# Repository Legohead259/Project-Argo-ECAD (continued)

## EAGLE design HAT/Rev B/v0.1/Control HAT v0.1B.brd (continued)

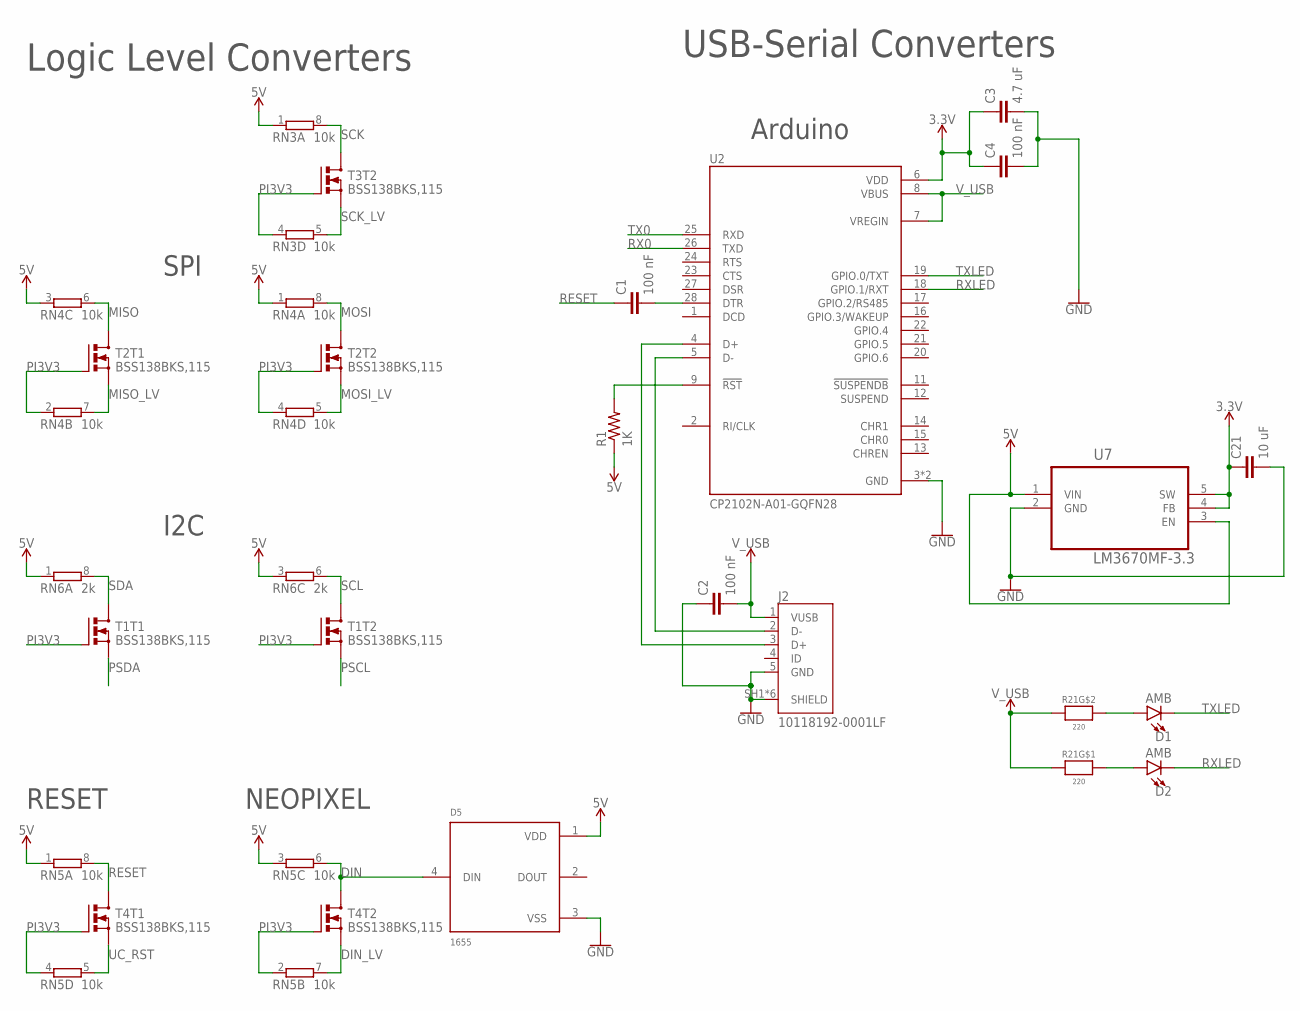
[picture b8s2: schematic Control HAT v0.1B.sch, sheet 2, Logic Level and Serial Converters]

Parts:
C1, C2, C4: 100 nF; C0603
C3: 4.7 uF; C0603
C21: 10 uF; C0603
D1, D2: AMB; LED-0603
D5: 1655; FCI_1655
J2: 10118192-0001LF; AMPHENOL_10118192-0001LF
R1: 1K; R0603
R21: 220; RESPACK_4X0603
RN3, RN4, RN5: 10k; EXB28V
RN6: 2k; EXB28V
T1, T2, T3, T4: BSS138BKS,115; SOT363
U2: CP2102N-A01-GQFN28; QFN50P500X500X80-29N
U7: LM3670MF-3.3; SOT95P284X122-5N

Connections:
3.3V: C3.1, C4.1, C21.1, U2.6 (VDD), U7.4 (FB), U7.5 (SW)
5V: D5.1 (VDD), R1.1, RN3.1, RN4.1, RN4.3 (1), RN5.1, RN5.3 (1), RN6.1, RN6.3 (1), U7.1 (VIN), U7.3 (EN); also elsewhere on the board
DIN: D5.4 (DIN), RN5.6 (2), T4.3 (D); also elsewhere on the board
DIN_LV: RN5.7 (2), T4.4 (S); also elsewhere on the board
GND: C2.1, C3.2, C4.2, C21.2, D5.3 (VSS), J2.5 (GND), J2.SH1 (SHIELD), J2.SH2 (SHIELD), J2.SH3 (SHIELD), J2.SH4 (SHIELD), J2.SH5 (SHIELD), J2.SH6 (SHIELD), U2.3 (GND), U2.29 (GND), U7.2 (GND); also elsewhere on the board
MISO: RN4.6 (2), T2.6 (D); also elsewhere on the board
MISO_LV: RN4.7 (2), T2.1 (S); also elsewhere on the board
MOSI: RN4.8 (2), T2.3 (D); also elsewhere on the board
MOSI_LV: RN4.5 (2), T2.4 (S); also elsewhere on the board
unnamed: J2.2 (D-), U2.5 (D-)
unnamed: J2.3 (D+), U2.4 (D+)
unnamed: R1.2, U2.9 (!RST)
unnamed: D1.A, R21.7 (2)
unnamed: D2.A, R21.8 (2)
unnamed: C1.2, U2.28 (DTR)
PI3V3: RN3.4 (1), RN4.2 (1), RN4.4 (1), RN5.2 (1), RN5.4 (1), T1.2 (G), T1.5 (G), T2.2 (G), T2.5 (G), T3.5 (G), T4.2 (G), T4.5 (G); also elsewhere on the board
PSCL: T1.4 (S); also elsewhere on the board
PSDA: T1.1 (S); also elsewhere on the board
RESET: C1.1, RN5.8 (2), T4.6 (D); also elsewhere on the board
RX0: U2.26 (TXD); also elsewhere on the board
RXLED: D2.C, U2.18 (GPIO.1/RXT)
SCK: RN3.8 (2), T3.3 (D); also elsewhere on the board
SCK_LV: RN3.5 (2), T3.4 (S); also elsewhere on the board
SCL: RN6.6 (2), T1.3 (D); also elsewhere on the board
SDA: RN6.8 (2), T1.6 (D); also elsewhere on the board
TX0: U2.25 (RXD); also elsewhere on the board
TXLED: D1.C, U2.19 (GPIO.0/TXT)
UC_RST: RN5.5 (2), T4.1 (S); also elsewhere on the board
V_USB: C2.2, J2.1 (VUSB), R21.1, R21.2 (1), U2.7 (VREGIN), U2.8 (VBUS)

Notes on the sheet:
Logic Level Converters
I2C
SPI
RESET
NEOPIXEL
USB-Serial Converters
Arduino

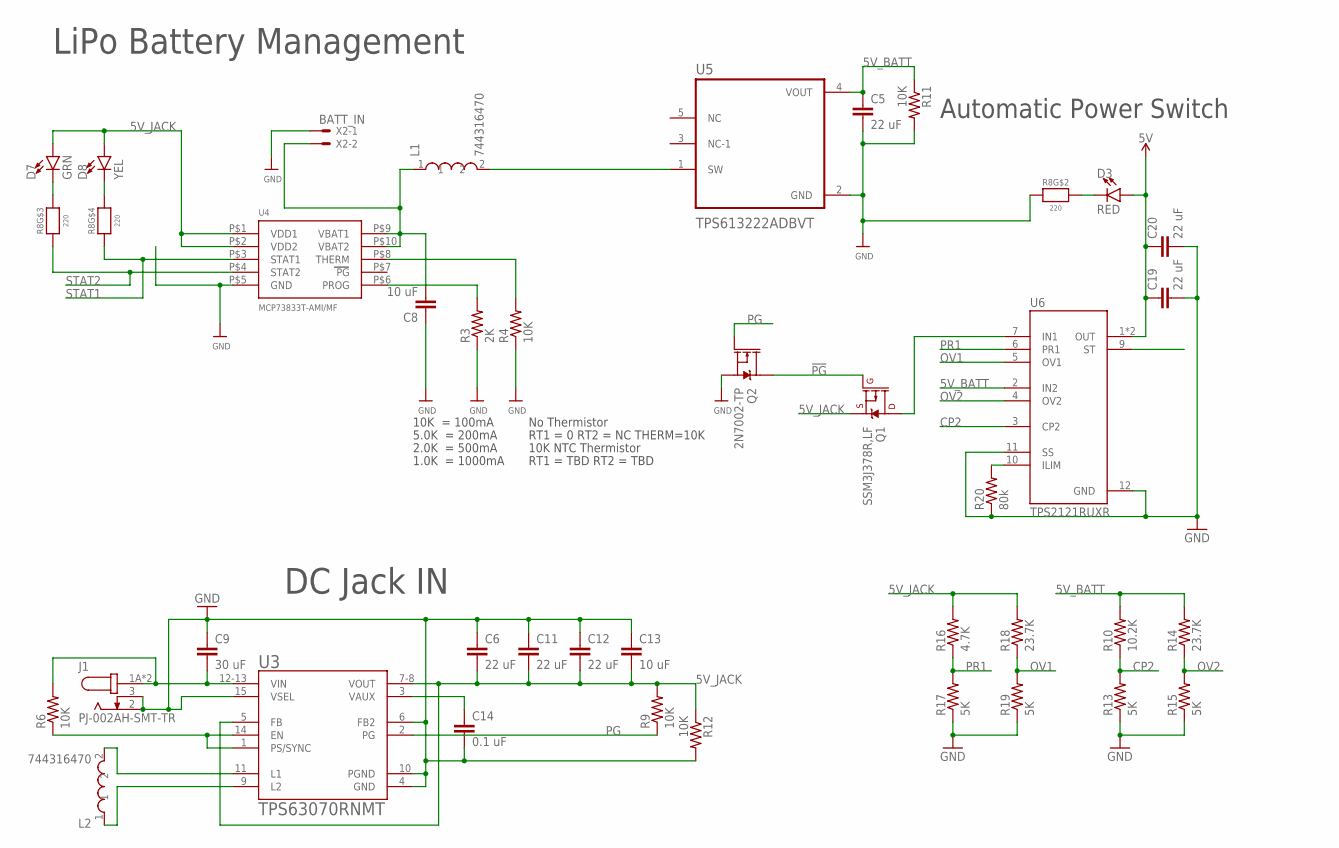
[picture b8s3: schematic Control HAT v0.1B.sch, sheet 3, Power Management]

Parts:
C5, C6, C11, C12, C19, C20: 22 uF; C0603
C8, C13: 10 uF; C0603
C9: 30 uF; C0603
C14: 0.1 uF; C0603
D3: RED; LED-0603
D7: GRN; LED-0603
D8: YEL; LED-0603
J1: PJ-002AH-SMT-TR; CUI_PJ-002AH-SMT-TR
L1, L2: 744316470; INDC2220X16
Q1: SSM3J378R,LF; SOT23-3
Q2: 2N7002-TP; SOT23-3
R3: 2K; R0603
R4, R6, R9, R11, R12: 10K; R0603
R8: 220; RESPACK_4X0603
R10: 10.2K; R0603
R13, R15, R17, R19: 5K; R0603
R14, R18: 23.7K; R0603
R16: 4.7K; R0603
R20: 80k; R0603
U3: TPS63070RNMT; QFN50P250X300X100-15N
U4: MCP73833T-AMI/MF; DFN10_3X3MM
U5: TPS613222ADBVT; SOT95P280X145-5N
U6: TPS2121RUXR; IC_TPS2121RUXR
X2: BATT_IN; JST-XH-02-PACKAGE-LONG-PAD

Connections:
5V: C19.1, C20.1, D3.A, U6.1 (OUT), U6.8 (OUT); also elsewhere on the board
5V_BATT: C5.1, R10.2, R11.1, R14.2, U5.4 (VOUT), U6.2 (IN2)
5V_JACK: C6.2, C11.2, C12.2, C13.2, D7.A, D8.A, Q1.2 (S), R9.2, R12.1, R16.2, R18.2, U3.5 (FB), U3.7-8 (VOUT), U4.P$1 (VDD1), U4.P$2 (VDD2)
!PG: Q1.1 (G), Q2.3 (D)
BATT: C8.2, L1.1, U4.P$9 (VBAT1), U4.P$10 (VBAT2), X2.2
CP2: R10.1, R13.2, U6.3 (CP2)
GND: C5.2, C6.1, C8.1, C9.1, C11.1, C12.1, C13.1, C14.2, C19.2, C20.2, J1.2, J1.3, Q2.2 (S), R3.1, R4.1, R8.2 (1), R11.2, R12.2, R13.1, R15.1, R17.1, R19.1, R20.1, U3.4 (GND), U3.6 (FB2), U3.10 (PGND), U3.15 (VSEL), U4.P$5 (GND), U5.2 (GND), U6.11 (SS), U6.12 (GND), X2.1; also elsewhere on the board
unnamed: D7.C, R8.6 (2)
unnamed: C9.2, J1.1A (1), J1.1B (1), R6.2, U3.12-13 (VIN)
unnamed: D8.C, R8.5 (2)
unnamed: Q1.3 (D), U6.7 (IN1)
unnamed: D3.C, R8.7 (2)
unnamed: L2.2, U3.11 (L1)
unnamed: L2.1, U3.9 (L2)
unnamed: C14.1, U3.3 (VAUX)
unnamed: L1.2, U5.1 (SW)
unnamed: R3.2, U4.P$6 (PROG)
unnamed: R6.1, U3.1 (PS/SYNC), U3.14 (EN)
unnamed: R4.2, U4.P$8 (THERM)
unnamed: R20.2, U6.10 (ILIM)
OV1: R18.1, R19.2, U6.5 (OV1)
OV2: R14.1, R15.2, U6.4 (OV2)
PG: Q2.1 (G), R9.1, U3.2 (PG)
PR1: R16.1, R17.2, U6.6 (PR1)
STAT1: R8.4 (1), U4.P$3 (STAT1); also elsewhere on the board
STAT2: R8.3 (1), U4.P$4 (STAT2); also elsewhere on the board

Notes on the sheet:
10K = 100mA
5.0K = 200mA
2.0K = 500mA
1.0K = 1000mA
No Thermistor
RT1 = 0 RT2 = NC THERM=10K
10K NTC Thermistor
RT1 = TBD RT2 = TBD
LiPo Battery Management
DC Jack IN
Automatic Power Switch

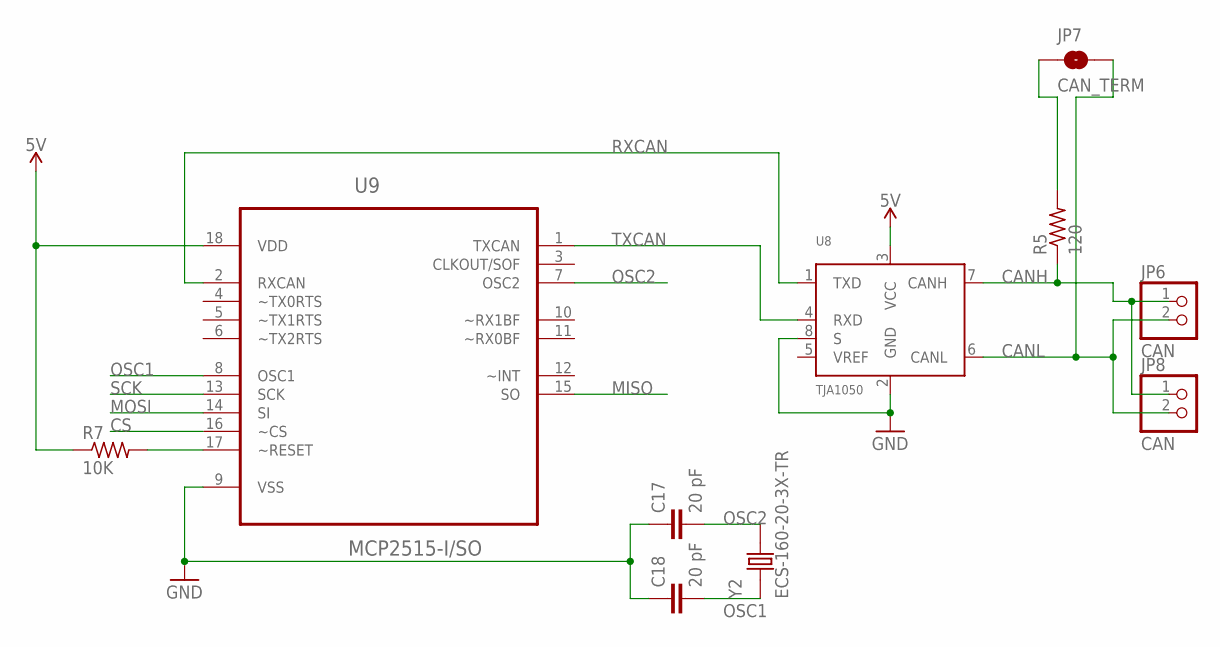
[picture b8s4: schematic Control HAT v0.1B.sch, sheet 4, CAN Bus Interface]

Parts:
C17, C18: 20 pF; C0603
JP6, JP8: CAN; 1X02
JP7: CAN_TERM; SMT-JUMPER_2_NO_NO-SILK
R5: 120; R0603
R7: 10K; R0603
U8: TJA1050; SOT96-1
U9: MCP2515-I/SO; SOIC127P1034X264-18N
Y2: ECS-160-20-3X-TR; XTAL_ECS-160-20-3X-TR

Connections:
5V: R7.1, U8.3 (VCC), U9.18 (VDD); also elsewhere on the board
CANH: JP6.1, JP8.1, R5.1, U8.7 (CANH)
CANL: JP6.2, JP7.2, JP8.2, U8.6 (CANL)
CS: U9.16 (~CS); also elsewhere on the board
GND: C17.1, C18.1, U8.2 (GND), U8.8 (S), U9.9 (VSS); also elsewhere on the board
MISO: U9.15 (SO); also elsewhere on the board
MOSI: U9.14 (SI); also elsewhere on the board
unnamed: JP7.1, R5.2
unnamed: R7.2, U9.17 (~RESET)
OSC1: C18.2, U9.8 (OSC1), Y2.1
OSC2: C17.2, U9.7 (OSC2), Y2.2
RXCAN: U8.1 (TXD), U9.2 (RXCAN)
SCK: U9.13 (SCK); also elsewhere on the board
TXCAN: U8.4 (RXD), U9.1 (TXCAN)

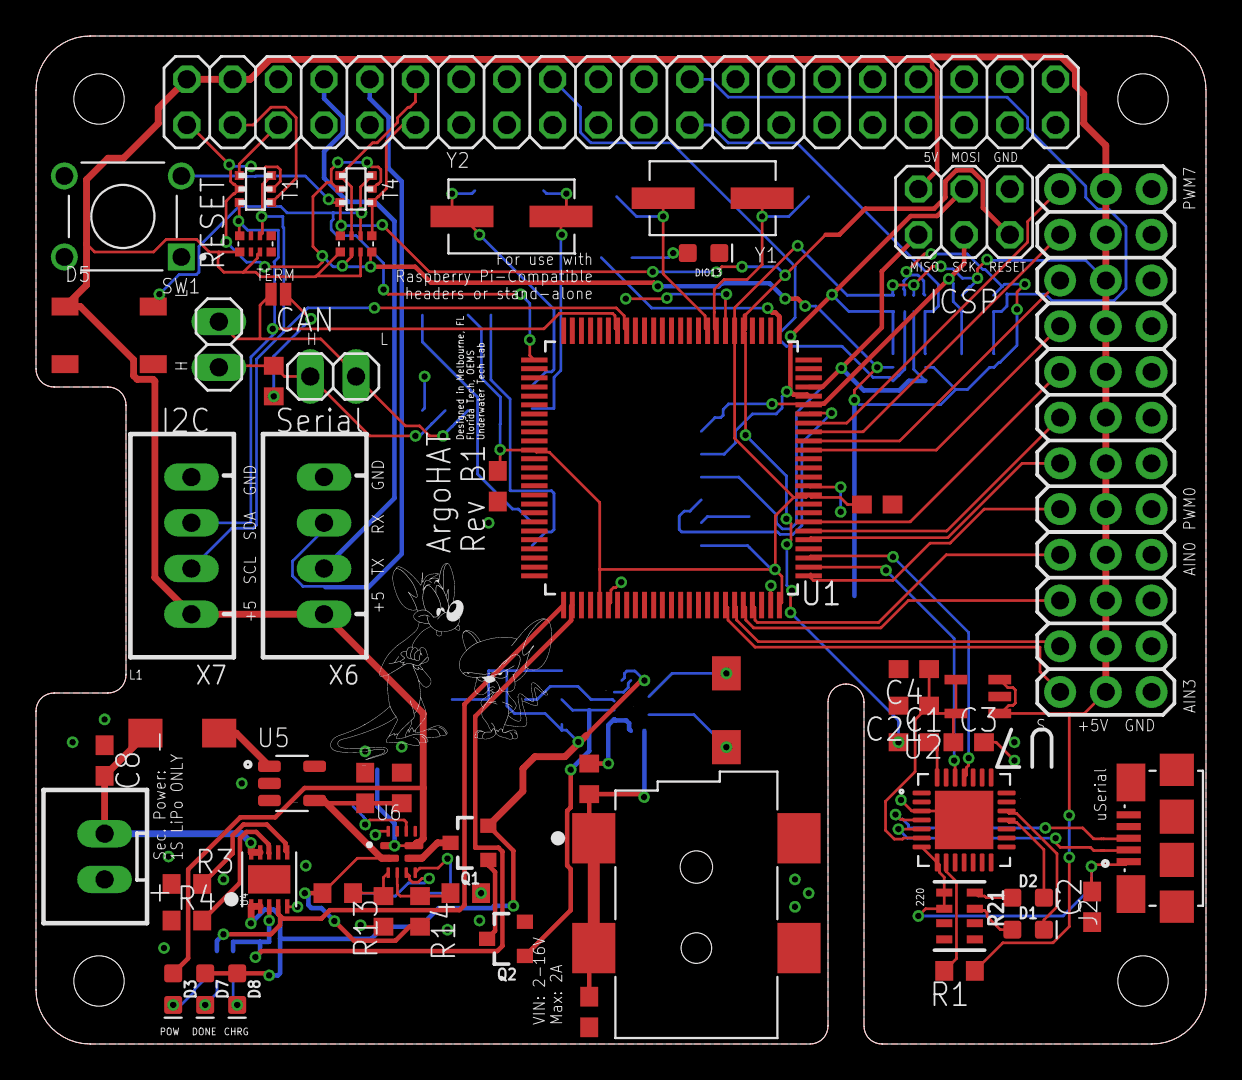
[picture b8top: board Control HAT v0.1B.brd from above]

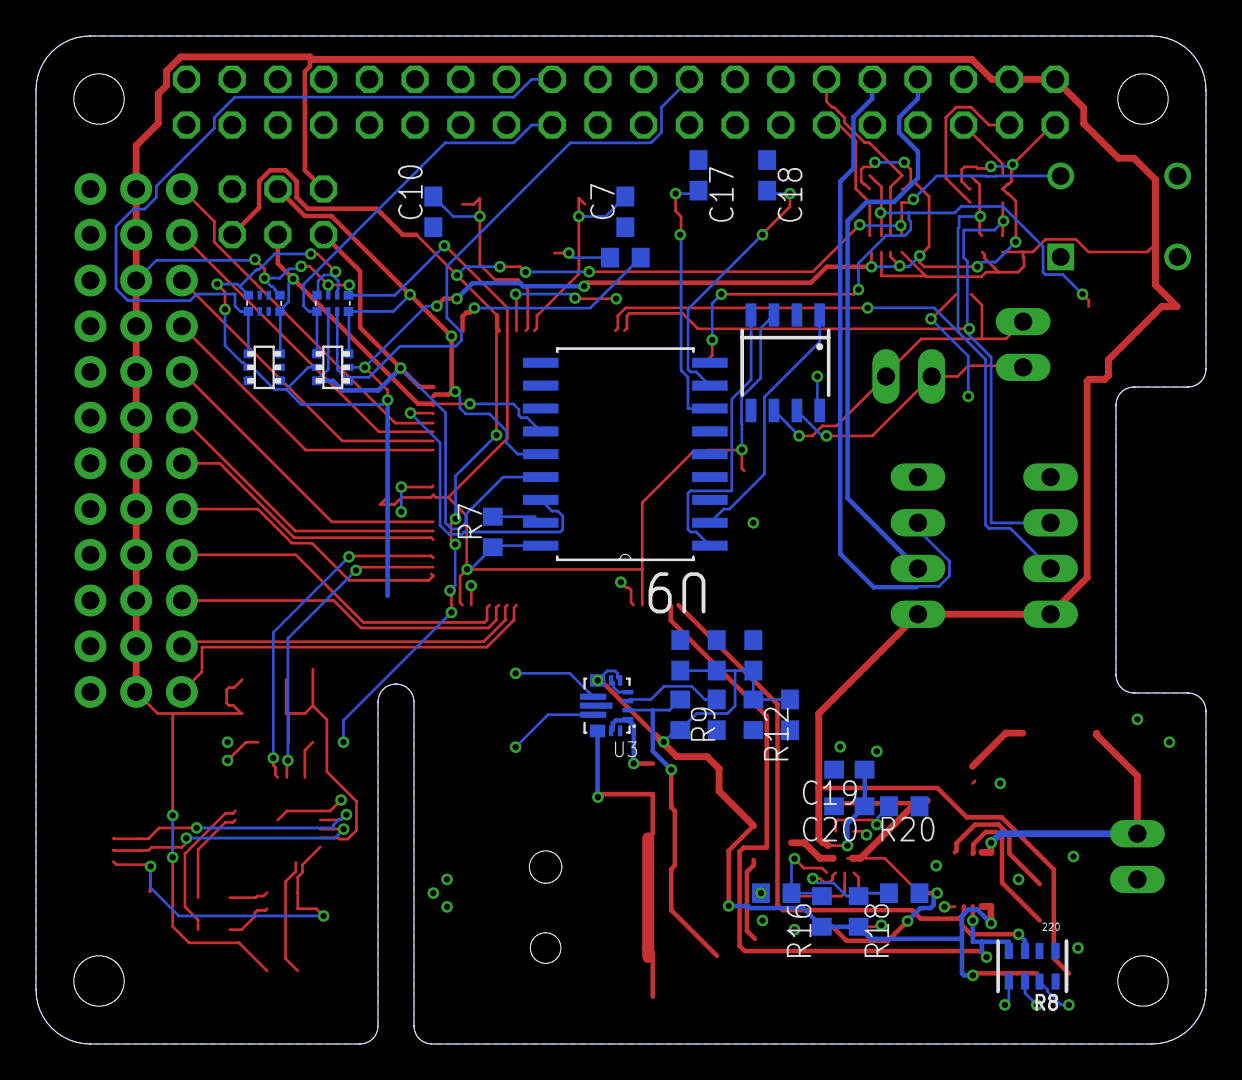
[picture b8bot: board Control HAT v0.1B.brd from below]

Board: 2 copper layers, 65.0 x 56.0 mm, 86 parts (28 on the bottom side), 80 nets.
